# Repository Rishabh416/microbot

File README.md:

# Microbot

My first fully custom project inspired by the microbots from the movie Big Hero 6. My goal is to get into swarm robotics and I believe this is a HUGE leap in that direction, but a good moment to learn. I made this project to learn about swarm robotics and the potential application in environmental applications such as in deserts. 

| Part Number | JLC Part Number | Description | Manufacturer | Package | URL |
| :--- | :--- | :--- | :--- | :--- | :--- |
| STM32F103C8T6 | C8734 | STM32 MCU | STMicroelectronics | LQFP-48(7x7) | [Link](https://jlcpcb.com/partdetail/STMicroelectronics-STM32F103C8T6/C8734) |
| N/A | N/A | Electromagnet | | | |
| | N/A | Servo Motor | | | |
| | N/A | DC Motor | | | |
| ICM-42688-P(TOKMAS) | C54308212 | IMU | Tokmas | LGA-14(2.5x3) | [Link](https://jlcpcb.com/partdetail/Tokmas-ICM_42688_P_TOKMAS/C54308212) |
| NRF24L01P-R | C8791 | NRF24 | Nordic Semicon | QFN-20-EP(4x4) | [Link](https://jlcpcb.com/partdetail/NordicSemicon-NRF24L01PR/C8791) |
| KH-204065-DZ | C530676 | Pogo Male | Shenzhen Kinghelm Elec | SMD, D=2mm | [Link](https://jlcpcb.com/partdetail/Shenzhen_KinghelmElec-KH_204065DZ/C530676) |
| BWCD-L4.5W2.0H2.3 | C2826546 | Pogo Female | BAT WIRELESS | SMD, D=2mm | [Link](https://jlcpcb.com/partdetail/BATWIRELESS-BWCD_L4_5W2_0H23/C2826546) |
| | N/A | LiPo Battery | | | |
| MCP73831-2ATI/MC | C635036 | BMS | Microchip Tech | DFN-8-EP(2x3) | [Link](https://jlcpcb.com/partdetail/MicrochipTech-MCP73831_2ATIMC/C635036) |
| XC6220B331MR-G | C86534 | Voltage Regulator | Torex Semicon | SOT-25 | [Link](https://jlcpcb.com/partdetail/TorexSemicon-XC6220B331MRG/C86534) |
| DRV8837CDSGR | C191000 | Motor Driver | Texas Instruments | WSON-8-EP(2x2) | [Link](https://jlcpcb.com/partdetail/TexasInstruments-DRV8837CDSGR/C191000) |
| 2450AT18A100E | C89334 | Antenna | Johanson Dielectrics | 1206 | [Link](https://jlcpcb.com/partdetail/JohansonDielectrics-2450AT18A100E/C89334) |
| 16M 12PF 10PPM | C2975359 | 16MHz Crystal | SST | HC-49S-SMD-2P-Mini | [Link](https://jlcpcb.com/partdetail/SST-16M_12PF10PPM/C2975359) |
| SSM3J338R,LF | C146352 | MOSFET | TOSHIBA | SOT-23F | [Link](https://jlcpcb.com/partdetail/TOSHIBA-SSM3J338RLF/C146352) |
| | | Capacitors | | 0603 | |
| HVRTB-3433EPX | C5246356 | Green LED | HONGLITRONIC | SMD-6P, 3.4x3.3mm | [Link](https://jlcpcb.com/partdetail/5956669-HVRTB3433EPX/C5246356) |
| | | Diodes | | D_SOD-323 | |
| TJ-S0704EX4T5ALC2R-A5 | C48689442 | Red LED | TOGIALED | 0201 | [Link](https://jlcpcb.com/partdetail/TOGIALED-TJ_S0704EX4T5ALC2RA5/C48689442) |
| 918-118A2021Y40002 | C399939 | USB C | Jing Extension | SMD | [Link](https://jlcpcb.com/partdetail/383027-918118A2021Y40002/C399939) |
| B2B-PH-K-S-GW | C5251182 | Conn_01x02 | JST | 插件, P=2mm | [Link](https://jlcpcb.com/partdetail/JST-B2B_PH_K_SGW/C5251182) |
| 2.54-1*3P针 | C49257 | Conn_01x03_Pin | BOOMELE | 插件, P=2.54mm | [Link](https://jlcpcb.com/partdetail/50265-2_54_1_3P/C49257) |
| 2.54-1*4 | C5116483 | Conn_01x04_Pin | ZHOURI | 插件, P=2.54mm | [Link](https://jlcpcb.com/partdetail/ZHOURI-2_54_14/C5116483) |
| | | Inductors | | 0603 | |
| | | Resistors | | 0603 | |

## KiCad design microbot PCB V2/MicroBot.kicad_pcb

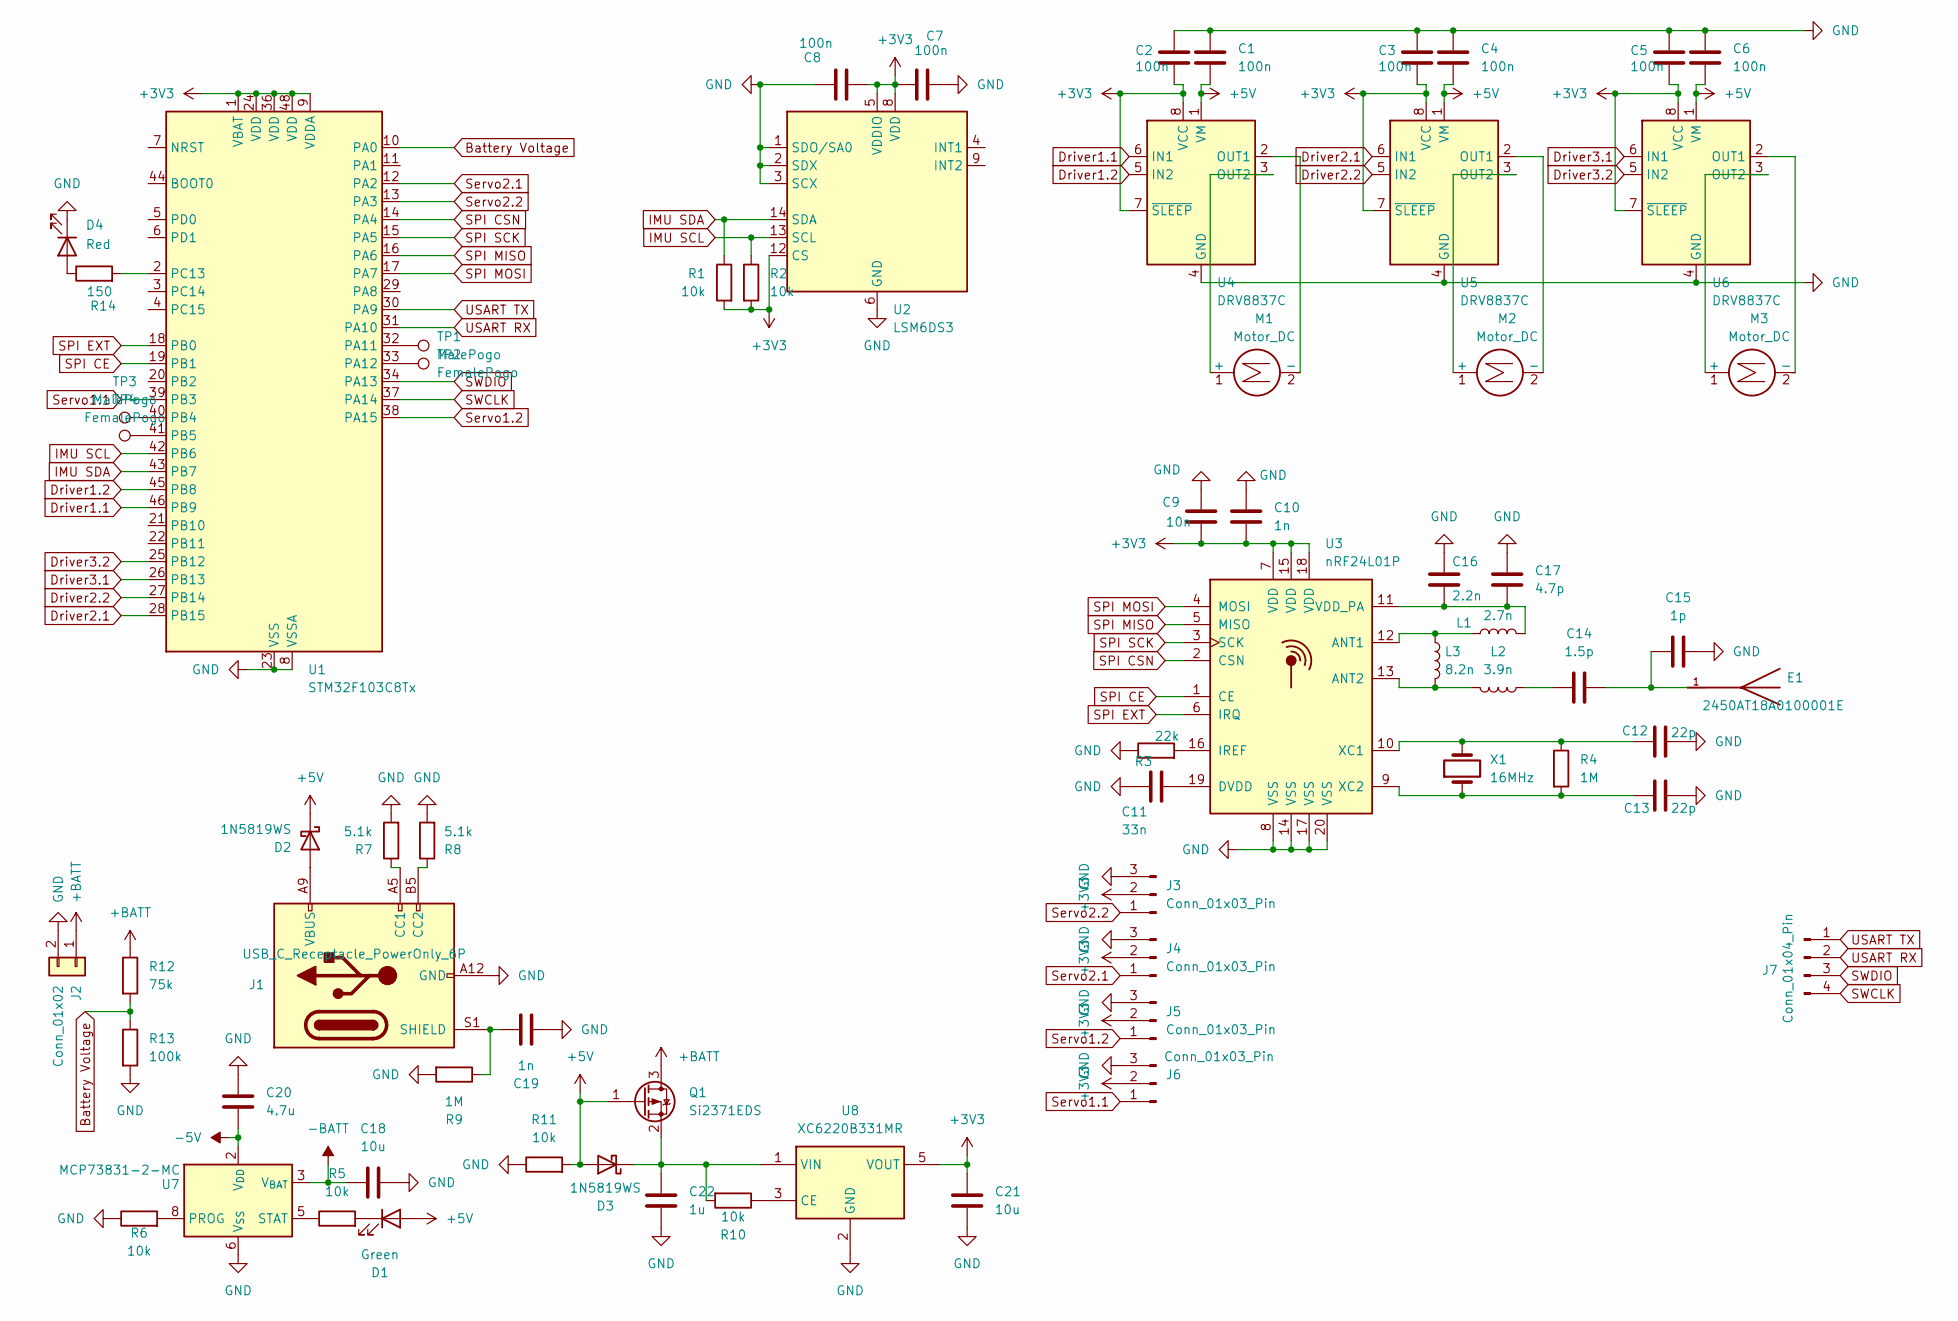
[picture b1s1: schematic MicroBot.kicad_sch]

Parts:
C1, C2, C3, C4, C5, C6, C7, C8: 100n; C_0603_1608Metric
C9: 10n; C_0603_1608Metric
C10, C19: 1n; C_0603_1608Metric
C11: 33n; C_0603_1608Metric
C12, C13: 22p; C_0603_1608Metric
C14: 1.5p; C_0603_1608Metric
C15: 1p; C_0603_1608Metric
C16: 2.2n; C_0603_1608Metric
C17: 4.7p; C_0603_1608Metric
C18, C21: 10u; C_0603_1608Metric
C20: 4.7u; C_0603_1608Metric
C22: 1u; C_0603_1608Metric
D1: Green; LED_0201_0603Metric
D2, D3: 1N5819WS; D_SOD-323
D4: Red; LED_0201_0603Metric
E1: 2450AT18A0100001E; XCVR_2450AT18A0100001E; PARTREV 4.0
J1: USB_C_Receptacle_PowerOnly_6P; USB_C_Plug_ShenzhenJingTuoJin_918-118A2021Y40002_Vertical
J2: Conn_01x02; JST_PH_B2B-PH-K_1x02_P2.00mm_Vertical
J3, J4, J5, J6: Conn_01x03_Pin; FanPinHeader_1x03_P2.54mm_Vertical
J7: Conn_01x04_Pin; PinHeader_1x04_P1.00mm_Vertical
L1: 2.7n; L_0603_1608Metric
L2: 3.9n; L_0603_1608Metric
L3: 8.2n; L_0603_1608Metric
M1, M2, M3: Motor_DC; TestPoint_2Pads_Pitch2.54mm_Drill0.8mm
Q1: Si2371EDS; SOT-23
R1, R2, R5, R6, R10, R11: 10k; R_0603_1608Metric
R3: 22k; R_0603_1608Metric
R4, R9: 1M; R_0603_1608Metric
R7, R8: 5.1k; R_0603_1608Metric
R12: 75k; R_0603_1608Metric
R13: 100k; R_0603_1608Metric
R14: 150; R_0603_1608Metric
TP1, TP3: MalePogo; PinHeader_1x01_P2.00mm_Vertical
TP2, TP4: FemalePogo; PinSocket_1x01_P2.00mm_Vertical
U1: STM32F103C8Tx; LQFP-48_7x7mm_P0.5mm
U2: LSM6DS3; LGA-14_3x2.5mm_P0.5mm_LayoutBorder3x4y
U3: nRF24L01P; QFN-20-1EP_4x4mm_P0.5mm_EP2.5x2.5mm
U4, U5, U6: DRV8837C; WSON-8-1EP_2x2mm_P0.5mm_EP0.9x1.6mm
U7: MCP73831-2-MC; DFN-8-1EP_3x2mm_P0.5mm_EP1.7x1.4mm
U8: XC6220B331MR; SOT-23-5
X1: 16MHz; Crystal_SMD_Abracon_ABM7-2Pin_6.0x3.5mm

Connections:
+3V3: C2.2, C3.2, C5.2, C7.1, C8.1, C9.1, C10.2, C21.1, J3.2, J4.2, J5.2, J6.2, R1.2, R2.2, U1.1 (VBAT), U1.9 (VDDA), U1.24 (VDD), U1.36 (VDD), U1.48 (VDD), U2.5 (VDDIO), U2.8 (VDD), U2.12 (CS), U3.7 (VDD), U3.15 (VDD), U3.18 (VDD), U4.7 (~SLEEP), U4.8 (VCC), U5.7 (~SLEEP), U5.8 (VCC), U6.7 (~SLEEP), U6.8 (VCC), U8.5 (VOUT)
+5V: C1.1, C4.1, C6.1, D1.2 (A), D2.1 (K), D3.2 (A), Q1.1 (G), R11.2, U4.1 (VM), U5.1 (VM), U6.1 (VM)
+BATT: J2.1, Q1.3 (D), R12.1
-5V: C20.1, U7.1 (V_{DD}), U7.2 (V_{DD})
-BATT: C18.1, U7.3 (V_{BAT}), U7.4 (V_{BAT})
Battery Voltage: R12.2, R13.1, U1.10 (PA0)
Driver1.1: U1.46 (PB9), U4.6 (IN1)
Driver1.2: U1.45 (PB8), U4.5 (IN2)
Driver2.1: U1.28 (PB15), U5.6 (IN1)
Driver2.2: U1.27 (PB14), U5.5 (IN2)
Driver3.1: U1.26 (PB13), U6.6 (IN1)
Driver3.2: U1.25 (PB12), U6.5 (IN2)
GND: C1.2, C2.1, C3.1, C4.2, C5.1, C6.2, C7.2, C8.2, C9.2, C10.1, C11.1, C12.2, C13.2, C15.2, C16.1, C17.1, C18.2, C19.1, C20.2, C21.2, C22.2, D4.1 (K), J1.A12 (GND), J1.B12 (GND), J2.2, J3.3, J4.3, J5.3, J6.3, R3.1, R6.1, R7.2, R8.2, R9.2, R11.1, R13.2, U1.8 (VSSA), U1.23 (VSS), U1.35 (VSS), U1.47 (VSS), U2.1 (SDO/SA0), U2.2 (SDX), U2.3 (SCX), U2.6 (GND), U2.7 (GND), U3.8 (VSS), U3.14 (VSS), U3.17 (VSS), U3.20 (VSS), U4.4 (GND), U4.9 (GND), U5.4 (GND), U5.9 (GND), U6.4 (GND), U6.9 (GND), U7.6 (V_{SS}), U8.2 (GND)
IMU SCL: R2.1, U1.42 (PB6), U2.13 (SCL)
IMU SDA: R1.1, U1.43 (PB7), U2.14 (SDA)
unnamed: C14.1, L2.1
unnamed: C14.2, C15.1, E1.1
unnamed: D1.1 (K), R5.2
unnamed: D2.2 (A), J1.A9 (VBUS), J1.B9 (VBUS)
unnamed: C22.1, D3.1 (K), Q1.2 (S), R10.2, U8.1 (VIN)
unnamed: D4.2 (A), R14.1
unnamed: J1.A5 (CC1), R7.1
unnamed: J1.B5 (CC2), R8.1
unnamed: C19.2, J1.S1 (SHIELD), R9.1
unnamed: M1.1 (+), U4.3 (OUT2)
unnamed: M1.2 (-), U4.2 (OUT1)
unnamed: M2.1 (+), U5.3 (OUT2)
unnamed: M2.2 (-), U5.2 (OUT1)
unnamed: M3.1 (+), U6.3 (OUT2)
unnamed: M3.2 (-), U6.2 (OUT1)
unnamed: TP1.1, U1.32 (PA11)
unnamed: TP2.1, U1.33 (PA12)
unnamed: TP3.1, U1.40 (PB4)
unnamed: TP4.1, U1.41 (PB5)
unnamed: R14.2, U1.2 (PC13)
unnamed: L1.1, L3.1, U3.12 (ANT1)
unnamed: L2.2, L3.2, U3.13 (ANT2)
unnamed: C11.2, U3.19 (DVDD)
unnamed: R3.2, U3.16 (IREF)
unnamed: C16.2, C17.2, L1.2, U3.11 (VDD_PA)
unnamed: C12.1, R4.1, U3.10 (XC1), X1.2
unnamed: C13.1, R4.2, U3.9 (XC2), X1.1
unnamed: R6.2, U7.8 (PROG)
unnamed: R5.1, U7.5 (STAT)
unnamed: R10.1, U8.3 (CE)
SPI CE: U1.19 (PB1), U3.1 (CE)
SPI CSN: U1.14 (PA4), U3.2 (CSN)
SPI EXT: U1.18 (PB0), U3.6 (IRQ)
SPI MISO: U1.16 (PA6), U3.5 (MISO)
SPI MOSI: U1.17 (PA7), U3.4 (MOSI)
SPI SCK: U1.15 (PA5), U3.3 (SCK)
SWCLK: J7.4, U1.37 (PA14)
SWDIO: J7.3, U1.34 (PA13)
Servo1.1: J6.1, U1.39 (PB3)
Servo1.2: J5.1, U1.38 (PA15)
Servo2.1: J4.1, U1.12 (PA2)
Servo2.2: J3.1, U1.13 (PA3)
USART RX: J7.2, U1.31 (PA10)
USART TX: J7.1, U1.30 (PA9)

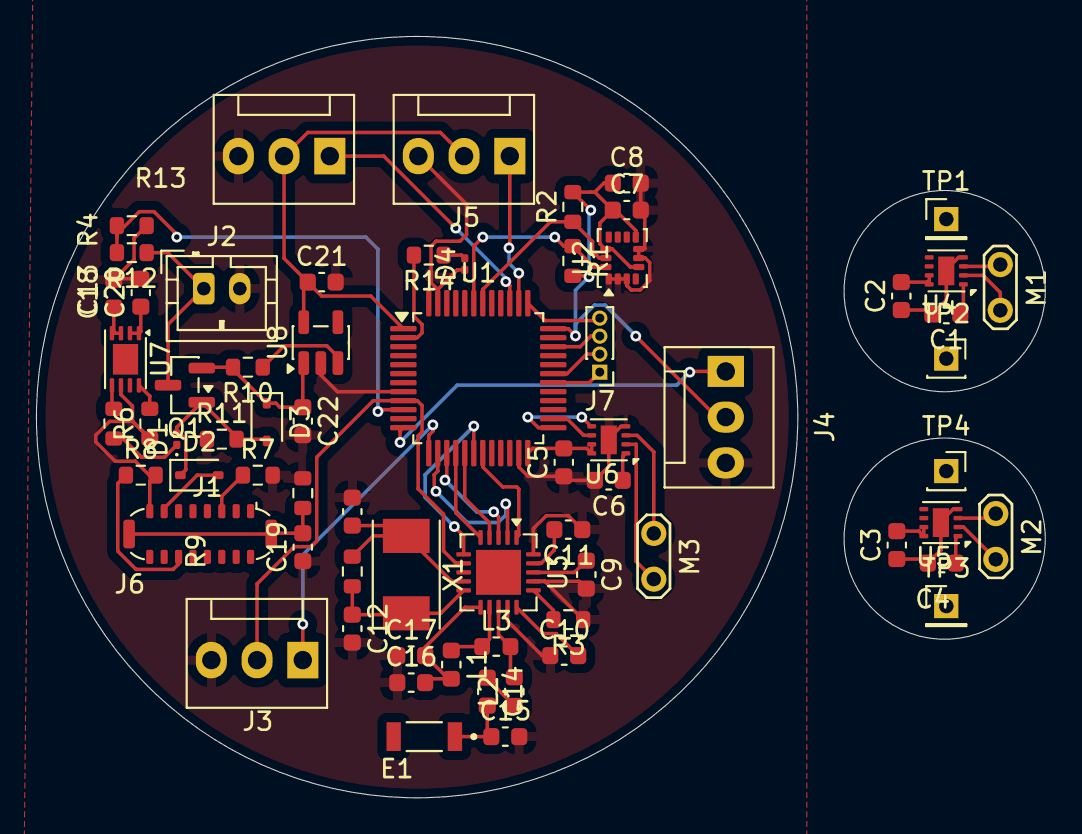
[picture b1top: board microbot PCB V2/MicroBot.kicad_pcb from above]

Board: 2 copper layers, 56.0 x 42.3 mm, 68 parts (0 on the bottom side), 59 nets.

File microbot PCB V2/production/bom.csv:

Designator,Footprint,Quantity,Value,LCSC Part #
"C1, C2, C3, C4, C5, C6, C7, C8",0603,8,100n,
"C10, C19",0603,2,1n,
C11,0603,1,33n,
"C12, C13",0603,2,22p,
C14,0603,1,1.5p,
C15,0603,1,1p,
C16,0603,1,2.2n,
C17,0603,1,4.7p,
"C18, C21",0603,2,10u,
C20,0603,1,4.7u,
C22,0603,1,1u,
C9,0603,1,10n,
D1,0201,1,Green,
"D2, D3",D_SOD-323,2,1N5819WS,
D4,0201,1,Red,
E1,XCVR_2450AT18A0100001E,1,2450AT18A0100001E,
J1,USB_C_Plug_ShenzhenJingTuoJin_918-118A2021Y40002_Vertical,1,USB_C_Receptacle_PowerOnly_6P,
J2,JST_PH_B2B-PH-K_1x02_P2.00mm_Vertical,1,Conn_01x02,
"J3, J4, J5, J6",FanPinHeader_1x03_P2.54mm_Vertical,4,Conn_01x03_Pin,
J7,PinHeader_1x04_P1.00mm_Vertical,1,Conn_01x04_Pin,
L1,0603,1,2.7n,
L2,0603,1,3.9n,
L3,0603,1,8.2n,
"M1, M2, M3",TestPoint_2Pads_Pitch2.54mm_Drill0.8mm,3,Motor_DC,
Q1,SOT-23,1,Si2371EDS,
"R1, R10, R11, R2, R5, R6",0603,6,10k,
R12,0603,1,75k,
R13,0603,1,100k,
R14,0603,1,150,
R3,0603,1,22k,
"R4, R9",0603,2,1M,
"R7, R8",0603,2,5.1k,
"TP1, TP3",PinHeader_1x01_P2.00mm_Vertical,2,MalePogo,
"TP2, TP4",PinSocket_1x01_P2.00mm_Vertical,2,FemalePogo,
U1,LQFP-48_7x7mm_P0.5mm,1,STM32F103C8Tx,
U2,LGA-14_3x2.5mm_P0.5mm_LayoutBorder3x4y,1,LSM6DS3,
U3,QFN-20-1EP_4x4mm_P0.5mm_EP2.5x2.5mm,1,nRF24L01P,
"U4, U5, U6",WSON-8-1EP_2x2mm_P0.5mm_EP0.9x1.6mm,3,DRV8837C,
U7,DFN-8-1EP_3x2mm_P0.5mm_EP1.7x1.4mm,1,MCP73831-2-MC,
U8,SOT-23-5,1,XC6220B331MR,
X1,Crystal_SMD_Abracon_ABM7-2Pin_6.0x3.5mm,1,16MHz,

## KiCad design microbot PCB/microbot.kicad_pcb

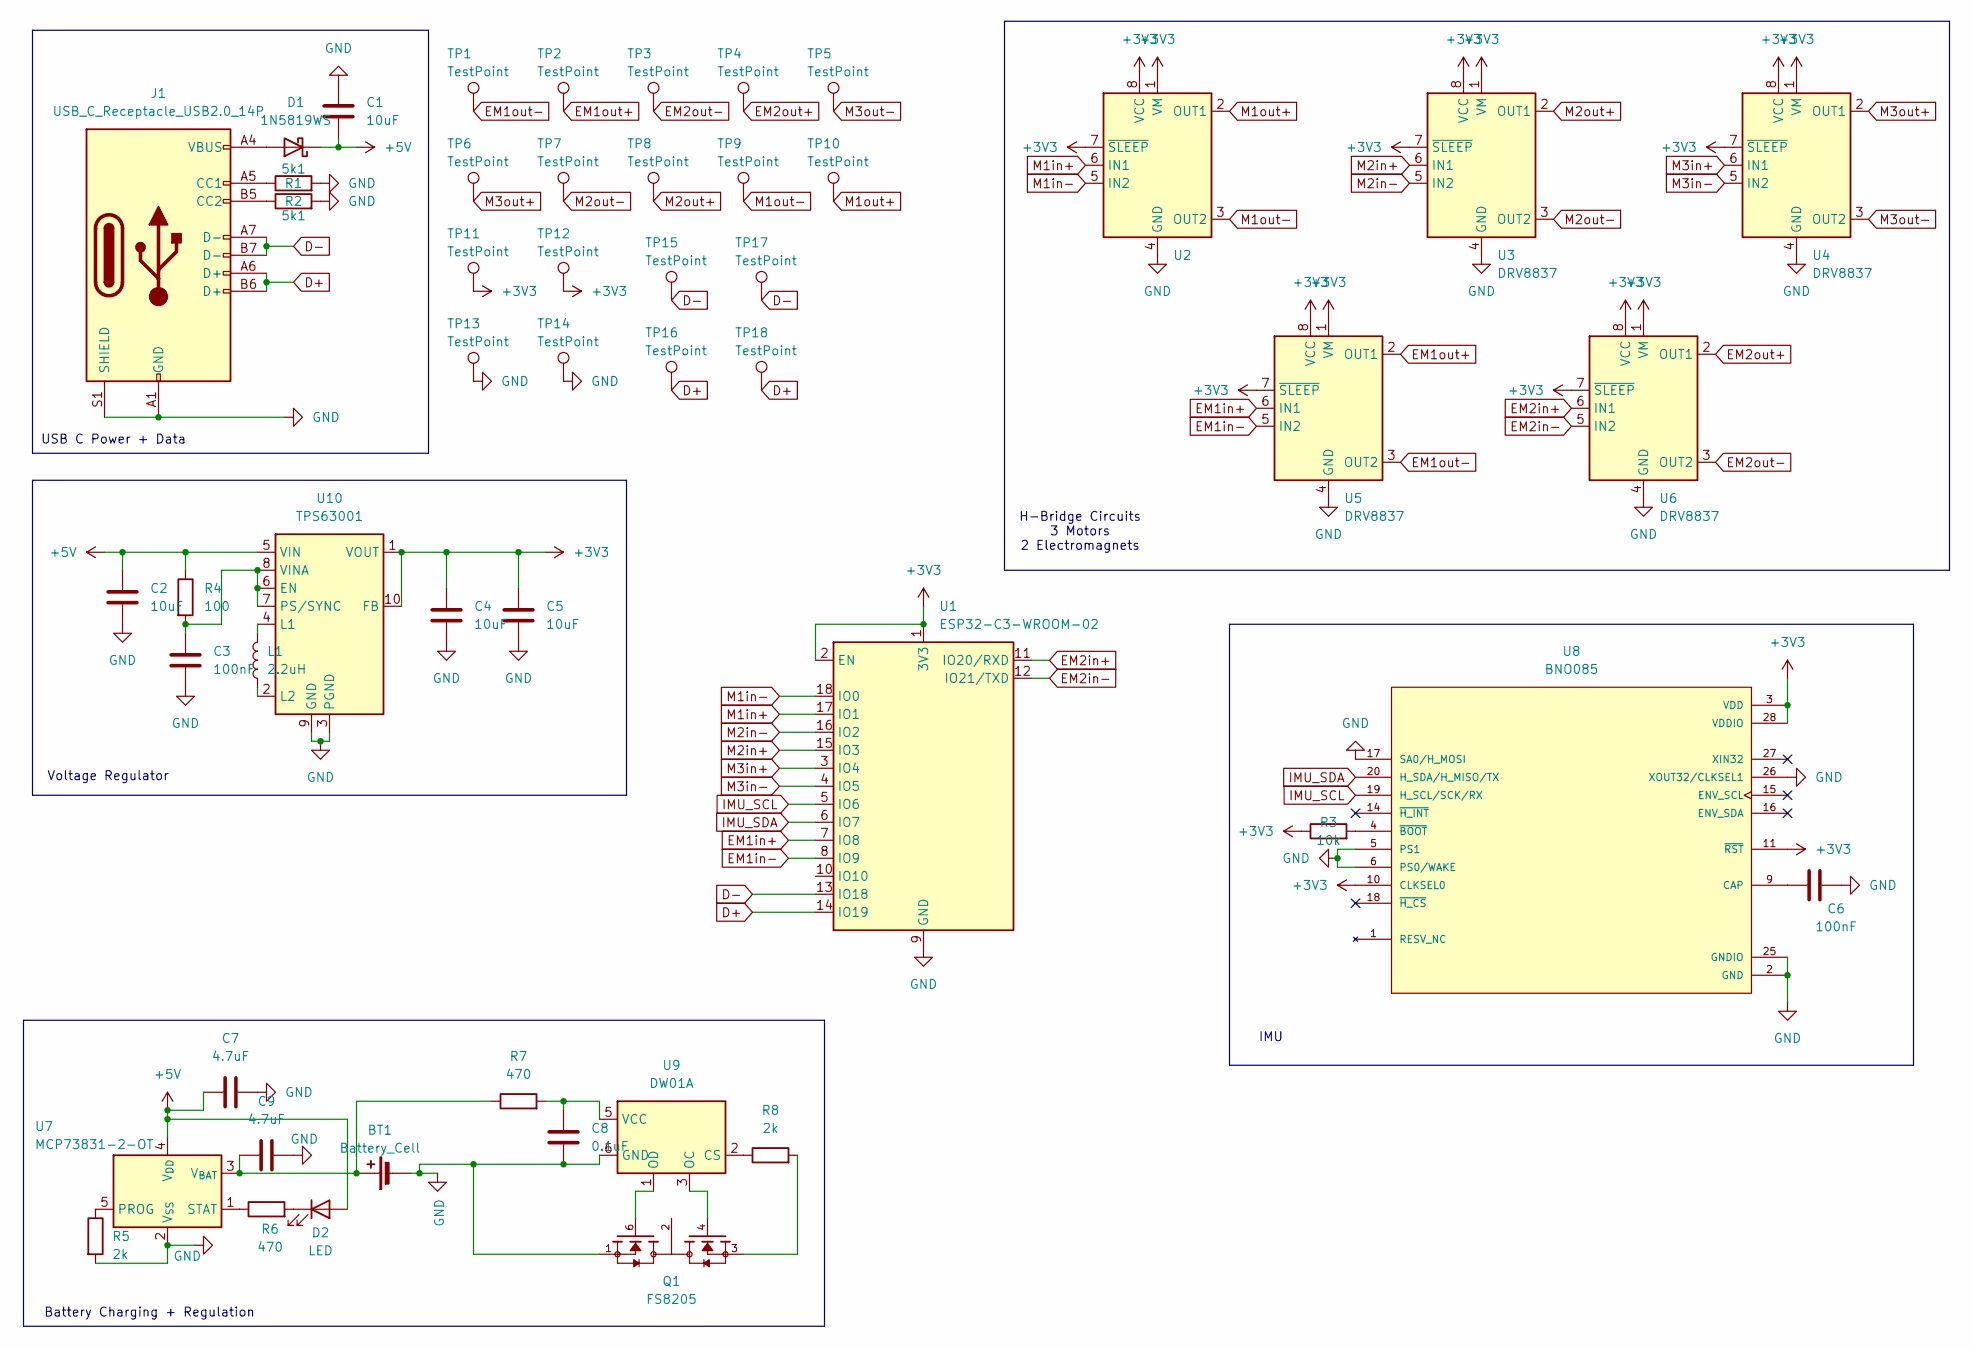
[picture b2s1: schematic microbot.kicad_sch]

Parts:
BT1: Battery_Cell; JST_EH_S2B-EH_1x02_P2.50mm_Horizontal
C1, C2, C4, C5: 10uF; C_0603_1608Metric
C3, C6: 100nF; C_0603_1608Metric
C7, C9: 4.7uF; C_0603_1608Metric
C8: 0.1uF; C_0603_1608Metric
D1: 1N5819WS; D_SOD-323
D2: LED; LED_0603_1608Metric
J1: USB_C_Receptacle_USB2.0_14P; USB_C_Receptacle_G-Switch_GT-USB-7051x
L1: 2.2uH; L_0603_1608Metric
Q1: FS8205; SOT95P280X145-6N; PARTREV 1.9
R1, R2: 5k1; R_0603_1608Metric
R3: 10k; R_0603_1608Metric
R4: 100; R_0603_1608Metric
R5, R8: 2k; R_0603_1608Metric
R6, R7: 470; R_0603_1608Metric
TP1, TP2, TP3, TP4, TP5, TP6, TP7, TP8, TP9, TP10, TP11, TP12, TP13, TP14, TP15, TP16, TP17, TP18: TestPoint; TestPoint_Pad_1.0x1.0mm
U1: ESP32-C3-WROOM-02
U2, U3, U4, U5, U6: DRV8837; WSON-8-1EP_2x2mm_P0.5mm_EP0.9x1.6mm
U7: MCP73831-2-OT; SOT-23-5
U8: BNO085; IC_BNO085; PARTREV v1.17
U9: DW01A; SOT-23-6
U10: TPS63001; Texas_DRC0010J_ThermalVias

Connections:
+3V3: C4.1, C5.1, R3.1, TP11.1, TP12.1, U1.1 (3V3), U1.2 (EN), U2.1 (VM), U2.7 (~SLEEP), U2.8 (VCC), U3.1 (VM), U3.7 (~SLEEP), U3.8 (VCC), U4.1 (VM), U4.7 (~SLEEP), U4.8 (VCC), U5.1 (VM), U5.7 (~SLEEP), U5.8 (VCC), U6.1 (VM), U6.7 (~SLEEP), U6.8 (VCC), U8.3 (VDD), U8.10 (CLKSEL0), U8.11 (~RST), U8.28 (VDDIO), U10.1 (VOUT), U10.10 (FB)
+5V: C1.2, C2.1, C7.1, D1.1 (K), D2.2 (A), R4.1, U7.4 (V_{DD}), U10.5 (VIN)
D+: J1.A6 (D+), J1.B6 (D+), TP16.1, TP18.1, U1.14 (IO19)
D-: J1.A7 (D-), J1.B7 (D-), TP15.1, TP17.1, U1.13 (IO18)
EM1in+: U1.7 (IO8), U5.6 (IN1)
EM1in-: U1.8 (IO9), U5.5 (IN2)
EM1out+: TP2.1, U5.2 (OUT1)
EM1out-: TP1.1, U5.3 (OUT2)
EM2in+: U1.11 (IO20/RXD), U6.6 (IN1)
EM2in-: U1.12 (IO21/TXD), U6.5 (IN2)
EM2out+: TP4.1, U6.2 (OUT1)
EM2out-: TP3.1, U6.3 (OUT2)
GND: BT1.2 (-), C1.1, C2.2, C3.2, C4.2, C5.2, C6.1, C7.2, C8.1, C9.2, J1.A1 (GND), J1.A12 (GND), J1.B1 (GND), J1.B12 (GND), J1.S1 (SHIELD), Q1.1, R1.2, R2.2, R5.2, TP13.1, TP14.1, U1.9 (GND), U1.19 (GND), U2.4 (GND), U2.9 (GND), U3.4 (GND), U3.9 (GND), U4.4 (GND), U4.9 (GND), U5.4 (GND), U5.9 (GND), U6.4 (GND), U6.9 (GND), U7.2 (V_{SS}), U8.2 (GND), U8.5 (PS1), U8.6 (PS0/WAKE), U8.17 (SA0/H_MOSI), U8.25 (GNDIO), U8.26 (XOUT32/CLKSEL1), U9.6 (GND), U10.3 (PGND), U10.9 (GND), U10.11 (PGND)
IMU_SCL: U1.5 (IO6), U8.19 (H_SCL/SCK/RX)
IMU_SDA: U1.6 (IO7), U8.20 (H_SDA/H_MISO/TX)
M1in+: U1.17 (IO1), U2.6 (IN1)
M1in-: U1.18 (IO0), U2.5 (IN2)
M1out+: TP10.1, U2.2 (OUT1)
M1out-: TP9.1, U2.3 (OUT2)
M2in+: U1.15 (IO3), U3.6 (IN1)
M2in-: U1.16 (IO2), U3.5 (IN2)
M2out+: TP8.1, U3.2 (OUT1)
M2out-: TP7.1, U3.3 (OUT2)
M3in+: U1.3 (IO4), U4.6 (IN1)
M3in-: U1.4 (IO5), U4.5 (IN2)
M3out+: TP6.1, U4.2 (OUT1)
M3out-: TP5.1, U4.3 (OUT2)
unnamed: BT1.1 (+), C9.1, R7.1, U7.3 (V_{BAT})
unnamed: D1.2 (A), J1.A4 (VBUS), J1.A9 (VBUS), J1.B4 (VBUS), J1.B9 (VBUS)
unnamed: D2.1 (K), R6.2
unnamed: J1.A5 (CC1), R1.1
unnamed: J1.B5 (CC2), R2.1
unnamed: Q1.2, Q1.5
unnamed: Q1.3, R8.2
unnamed: R5.1, U7.5 (PROG)
unnamed: R6.1, U7.1 (STAT)
unnamed: C6.2, U8.9 (CAP)
unnamed: R3.2, U8.4 (~BOOT)
unnamed: R8.1, U9.2 (CS)
unnamed: Q1.4, U9.3 (OC)
unnamed: Q1.6, U9.1 (OD)
unnamed: C8.2, R7.2, U9.5 (VCC)
unnamed: C3.1, R4.2, U10.6 (EN), U10.7 (PS/SYNC), U10.8 (VINA)
unnamed: L1.2, U10.4 (L1)
unnamed: L1.1, U10.2 (L2)

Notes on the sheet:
Battery Charging + Regulation
IMU
H-Bridge Circuits 3 Motors 2 Electromagnets
Voltage Regulator
USB C Power + Data

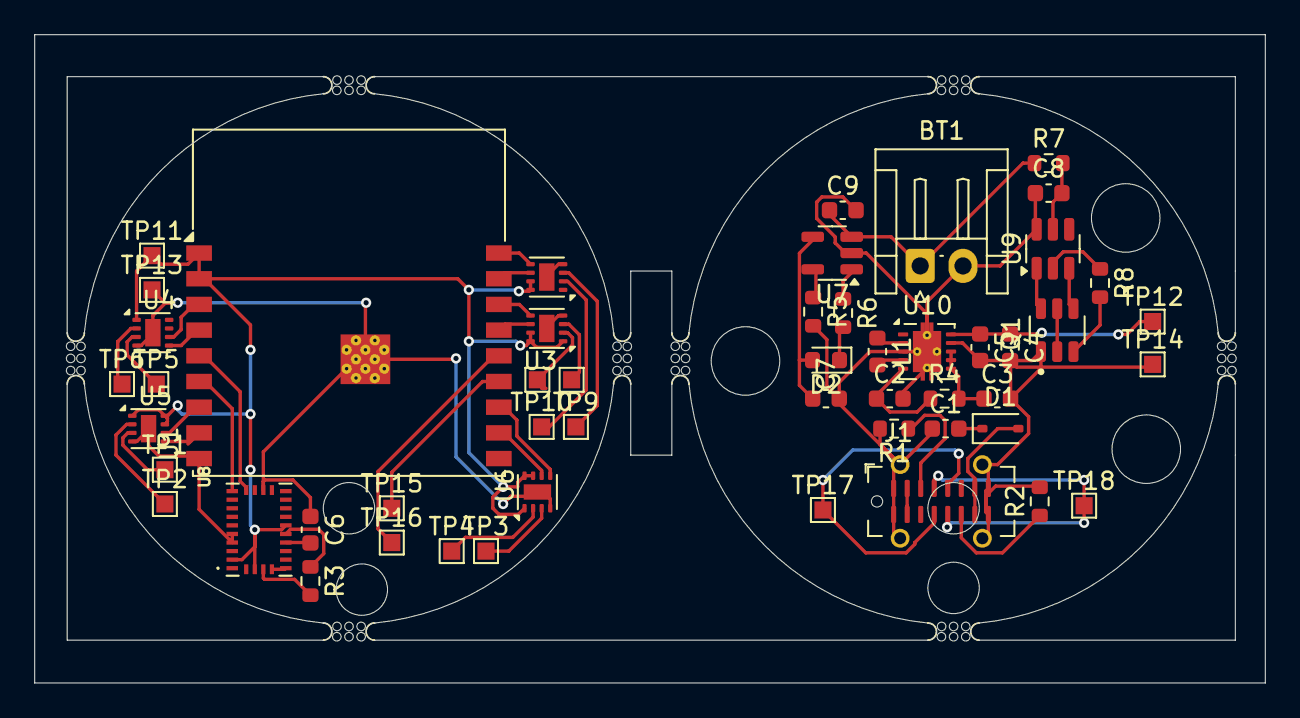
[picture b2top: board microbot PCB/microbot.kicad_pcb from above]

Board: 2 copper layers, 71.8 x 37.9 mm, 59 parts (0 on the bottom side), 45 nets.

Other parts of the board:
mouse-bite-1mm-3mm, mouse-bite-1mm-3mm#2, mouse-bite-1mm-3mm#3, mouse-bite-1mm-3mm#4, mouse-bite-1mm-3mm#5, mouse-bite-1mm-3mm#6, mouse-bite-1mm-3mm#7, mouse-bite-1mm-3mm#8: VAL**; mouse-bite-1mm-3mm

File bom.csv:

Designator,Footprint,Quantity,Value,LCSC Part #
BT1,JST_EH_S2B-EH_1x02_P2.50mm_Horizontal,1,Battery_Cell,
"C1, C2, C4, C5",603,4,10uF,
"C3, C6",603,2,100nF,
"C7, C9",603,2,4.7uF,
C8,603,1,0.1uF,
D1,D_SOD-323,1,1N5819WS,
D2,603,1,LED,
J1,USB_C_Receptacle_G-Switch_GT-USB-7051x,1,USB_C_Receptacle_USB2.0_14P,
L1,603,1,2.2uH,
"MOUSE-BITE-1MM-3MM_8, MOUSE-BITE-1MM-3MM_7, MOUSE-BITE-1MM-3MM_6, MOUSE-BITE-1MM-3MM_5, MOUSE-BITE-1MM-3MM_4, MOUSE-BITE-1MM-3MM_3, MOUSE-BITE-1MM-3MM_2, MOUSE-BITE-1MM-3MM",mouse-bite-1mm-3mm,8,VAL**,
Q1,SOT95P280X145-6N,1,FS8205,
"R1, R2",603,2,5k1,
R3,603,1,10k,
R4,603,1,100,
"R5, R8",603,2,2k,
"R6, R7",603,2,470,
"TP1, TP10, TP11, TP12, TP13, TP14, TP15, TP16, TP17, TP18, TP2, TP3, TP4, TP5, TP6, TP7, TP8, TP9",TestPoint_Pad_1.0x1.0mm,18,TestPoint,
U1,ESP32-C3-WROOM-02,1,ESP32-C3-WROOM-02,
U10,Texas_DRC0010J_ThermalVias,1,TPS63001,
"U2, U3, U4, U5, U6",WSON-8-1EP_2x2mm_P0.5mm_EP0.9x1.6mm,5,DRV8837,
U7,SOT-23-5,1,MCP73831-2-OT,
U8,IC_BNO085,1,BNO085,
U9,SOT-23-6,1,DW01A,
,Solenoid electromagnet,4,https://www.amazon.com/gp/product/B0F1YNQTFQ/ref=ox_sc_act_t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,
,Micro motor,4,https://www.amazon.com/gp/product/B09BDVHRV7/ref=ox_sc_act_t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,

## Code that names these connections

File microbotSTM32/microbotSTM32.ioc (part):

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Mcu.Name=STM32F103C(8-B)Tx
Mcu.Package=LQFP48
Mcu.UserName=STM32F103C8Tx
PA0-WKUP.GPIOParameters=GPIO_Label
PA0-WKUP.GPIO_Label=servo0
PA0-WKUP.Signal=S_TIM2_CH1_ETR
PA1.GPIOParameters=GPIO_Label
PA1.GPIO_Label=servo1
PA1.Signal=S_TIM2_CH2
PA10.Mode=Asynchronous
PA10.Signal=USART1_RX
PA2.GPIOParameters=GPIO_Label
PA2.GPIO_Label=servo2
PA2.Signal=S_TIM2_CH3
PA3.GPIOParameters=GPIO_Label
PA3.GPIO_Label=servo3
PA3.Signal=S_TIM2_CH4
PA5.Mode=Full_Duplex_Master
PA5.Signal=SPI1_SCK
PA6.Mode=Full_Duplex_Master
PA6.Signal=SPI1_MISO
PA7.Mode=Full_Duplex_Master
PA7.Signal=SPI1_MOSI
PA9.Mode=Asynchronous
PA9.Signal=USART1_TX
PB0.GPIOParameters=GPIO_ModeDefaultEXTI
PB0.GPIO_ModeDefaultEXTI=GPIO_MODE_IT_FALLING
PB0.Signal=GPXTI0
PB1.GPIOParameters=GPIO_Speed,GPIO_Label
PB1.GPIO_Label=CE
PB1.GPIO_Speed=GPIO_SPEED_FREQ_HIGH
PB1.Signal=GPIO_Output
PB10.GPIOParameters=GPIO_Speed,GPIO_Label
PB10.GPIO_Label=CSN
PB10.GPIO_Speed=GPIO_SPEED_FREQ_HIGH
PB10.Signal=GPIO_Output
PB3.Signal=GPIO_Output
PB4.Signal=GPIO_Output
PC13-TAMPER-RTC.Signal=GPIO_Output
RCC.SYSCLKFreq_VALUE=16000000
RCC.SYSCLKSource=RCC_SYSCLKSOURCE_PLLCLK
board=custom

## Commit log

2025-12-29 basic firmware to test actuation
2025-12-29 minor change
2025-12-30 added readme
2026-03-12 working LED blink
2026-03-13 working servo (needs calibration) and magnet
2026-03-18 working radio communication
2026-03-31 Updated files for V2
